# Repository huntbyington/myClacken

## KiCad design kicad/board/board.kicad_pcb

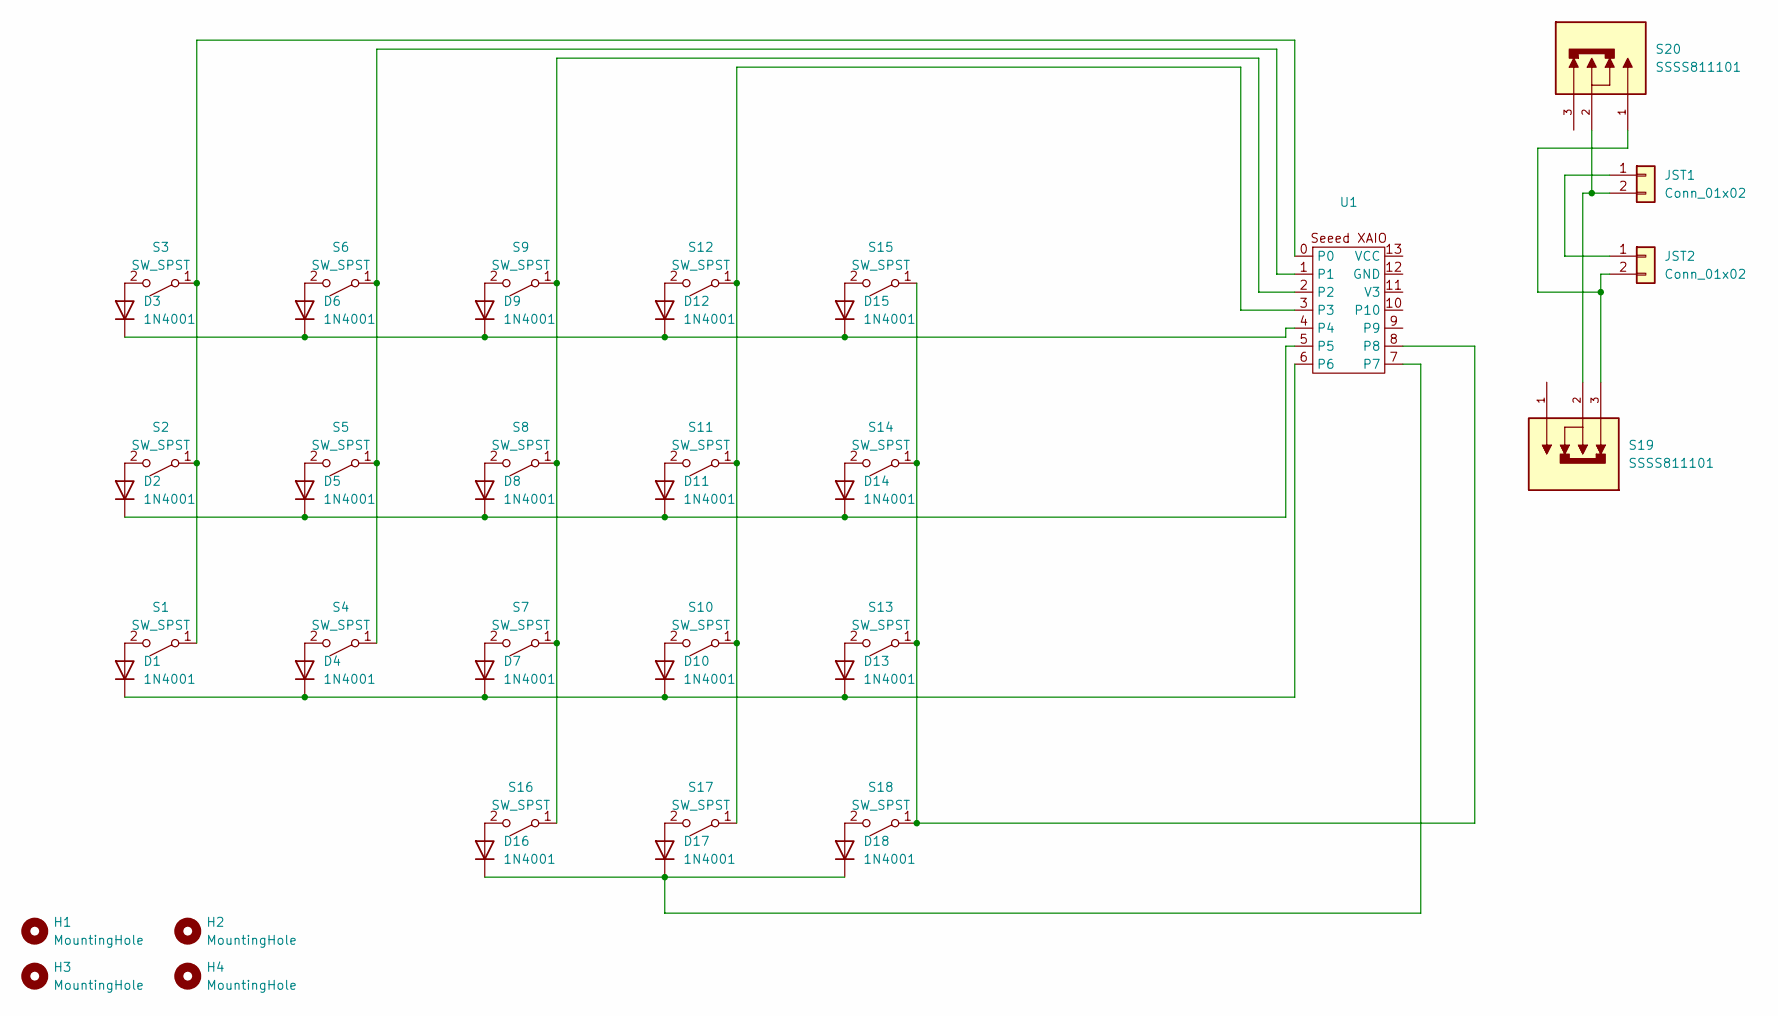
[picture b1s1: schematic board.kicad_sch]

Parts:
D1, D2, D3, D4, D5, D6, D7, D8, D9, D10, D11, D12, D13, D14, D15, D16, D17, D18: 1N4001; reversable_diode
H1, H2, H3, H4: MountingHole; MountingHole_2.2mm_M2
JST1, JST2: Conn_01x02; JST_angled
S1, S2, S3, S4, S5, S6, S7, S8, S9, S10, S11, S12, S13, S14, S15, S16, S17, S18: SW_SPST; choc_switches
S19, S20: SSSS811101; SW_SSSS811101; PARTREV N/A
U1: seeed_xaio

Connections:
unnamed: D1.2 (A), S1.2 (B)
unnamed: D1.1 (K), D4.1 (K), D7.1 (K), D10.1 (K), D13.1 (K), U1.6
unnamed: D2.2 (A), S2.2 (B)
unnamed: D3.2 (A), S3.2 (B)
unnamed: D4.2 (A), S4.2 (B)
unnamed: D5.2 (A), S5.2 (B)
unnamed: D6.2 (A), S6.2 (B)
unnamed: D7.2 (A), S7.2 (B)
unnamed: D8.2 (A), S8.2 (B)
unnamed: D9.2 (A), S9.2 (B)
unnamed: D10.2 (A), S10.2 (B)
unnamed: D11.2 (A), S11.2 (B)
unnamed: D2.1 (K), D5.1 (K), D8.1 (K), D11.1 (K), D14.1 (K), U1.5
unnamed: D12.2 (A), S12.2 (B)
unnamed: D3.1 (K), D6.1 (K), D9.1 (K), D12.1 (K), D15.1 (K), U1.4
unnamed: D13.2 (A), S13.2 (B)
unnamed: D14.2 (A), S14.2 (B)
unnamed: D15.2 (A), S15.2 (B)
unnamed: D16.2 (A), S16.2 (B)
unnamed: D16.1 (K), D17.1 (K), D18.1 (K), U1.7
unnamed: D17.2 (A), S17.2 (B)
unnamed: D18.2 (A), S18.2 (B)
unnamed: JST1.1, JST2.1
unnamed: JST1.2, S19.2, S20.2
unnamed: JST2.2, S19.3, S20.1
unnamed: S1.1 (A), S2.1 (A), S3.1 (A), U1.0
unnamed: S4.1 (A), S5.1 (A), S6.1 (A), U1.1
unnamed: S10.1 (A), S11.1 (A), S12.1 (A), S17.1 (A), U1.3
unnamed: S13.1 (A), S14.1 (A), S15.1 (A), S18.1 (A), U1.8
unnamed: S7.1 (A), S8.1 (A), S9.1 (A), S16.1 (A), U1.2

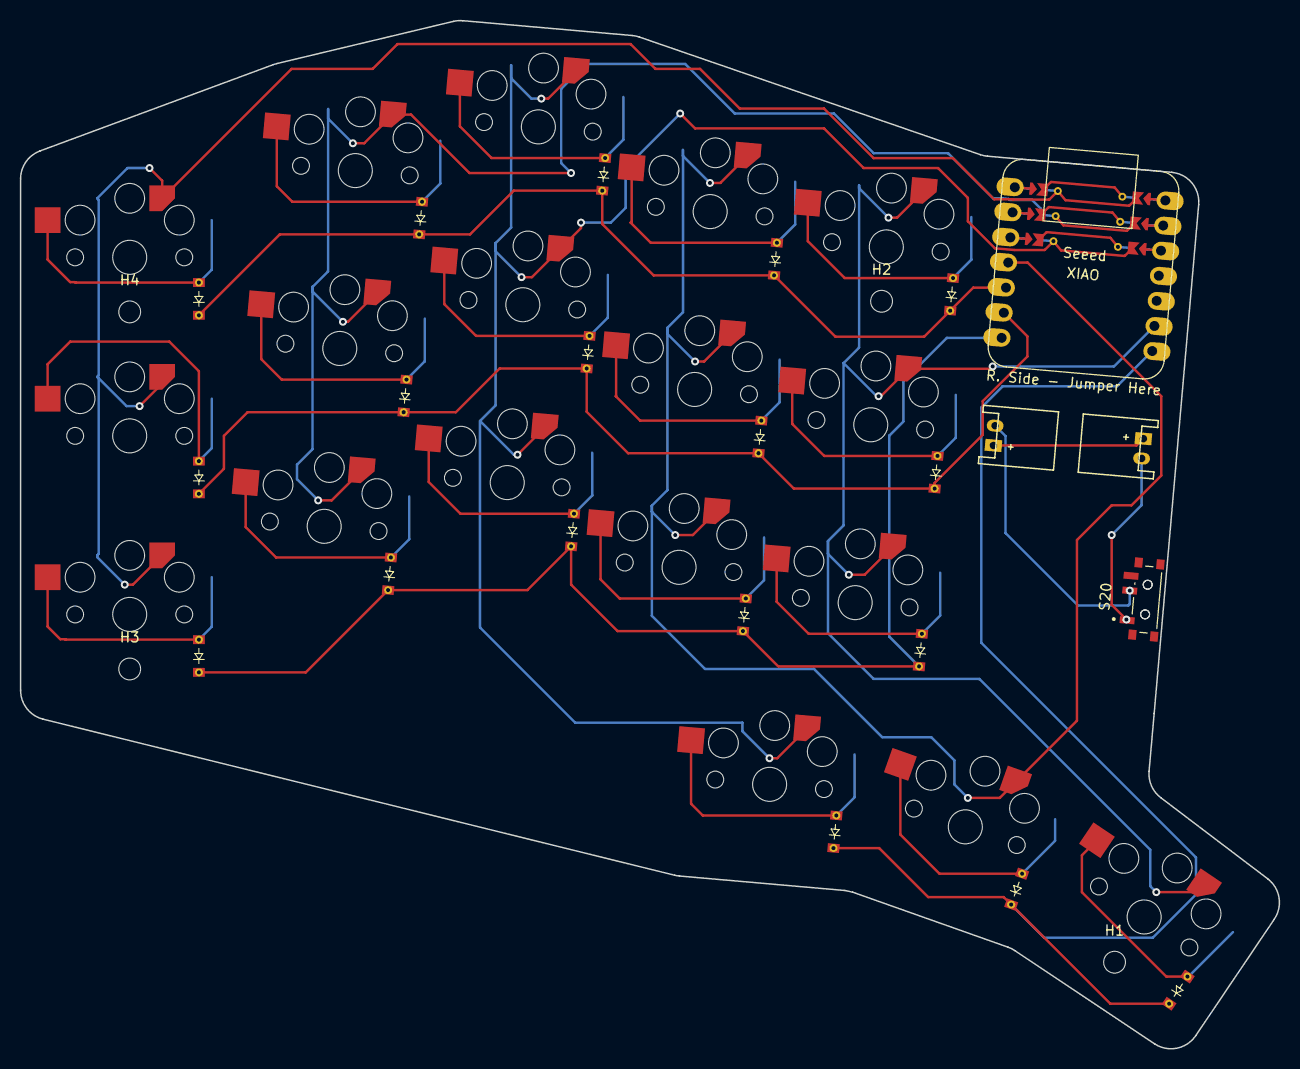
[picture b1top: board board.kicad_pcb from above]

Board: 2 copper layers, 126.9 x 103.7 mm, 45 parts (1 on the bottom side), 30 nets.

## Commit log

2024-11-07 Clacken w/ Completed Schematic
2024-11-14 Keyboard with Traces
2024-11-22 fixed wiring
